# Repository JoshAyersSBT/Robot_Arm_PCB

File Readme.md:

# USB-C PD Powered ESP32 Servo Controller

This document consolidates the **power architecture, wiring, BOM additions, and system diagram** for an ESP32-based robot arm controller using:

* **USB-C Power Delivery (PD)** via **STUSB4500QTR**
* **ESP32** MCU
* **PCA9685** PWM servo controller
* **CH340X** USB-to-UART programmer
* **Cheap / low-load servos** (budget-friendly design)

---

## 1. System Overview

The board negotiates a higher-voltage USB-C PD contract, then generates two isolated rails:

* **SERVO_6V** – high-current rail for servos
* **+3V3** – logic rail for ESP32, PCA9685, and STUSB4500

Key design goal: **prevent ESP32 brownout** caused by servo current spikes.

---

## 2. Power Domains

### Rails

* **VBUS_IN**: USB-C VBUS (5–20V after PD negotiation)
* **VSYS**: Post power-path rail
* **SERVO_6V**: Buck-regulated servo rail
* **+3V3**: Logic rail

### Critical Rules

* ESP32 **must only see 3.3V**
* Servo power **must not be drawn from 3.3V**
* Servo current must not share thin traces or return paths with ESP32 logic ground

---

## 3. Wiring Map (Net-Level)

### USB-C → STUSB4500QTR (PD)

* `USBC_CC1 (A5)  -> STUSB_CC1`
* `USBC_CC2 (B5)  -> STUSB_CC2`
* `USBC_VBUS      -> VBUS_IN`
* `USBC_GND       -> GND`

### USB-C → CH340X (USB2)

* `USBC_D+ (A6/B6 tied) -> CH340_UD+`
* `USBC_D− (A7/B7 tied) -> CH340_UD−`

### CH340X → ESP32 (UART)

* `CH340_TXD -> ESP32_U0RXD (GPIO3)`
* `CH340_RXD -> ESP32_U0TXD (GPIO1)`
* `CH340_DTR/RTS -> ESP32_EN / ESP32_IO0 (auto-program circuit)`

### ESP32 ↔ STUSB4500QTR (I2C + Status)

* `ESP32_GPIO21 (SDA) <-> STUSB_SDA` (pull-up to +3V3)
* `ESP32_GPIO22 (SCL) <-> STUSB_SCL` (pull-up to +3V3)
* `STUSB_ALERT -> ESP32_GPIO (input, optional)`
* `ESP32_GPIO -> STUSB_RESET (optional; otherwise pull-up)`

### ESP32 ↔ PCA9685 (I2C)

* `ESP32_GPIO21 (SDA) <-> PCA_SDA`
* `ESP32_GPIO22 (SCL) <-> PCA_SCL`
* `PCA_VDD -> +3V3`
* `PCA_V+  -> SERVO_6V`
* `PCA_GND -> GND`

### Power Chain

* `VBUS_IN -> Power Path -> VSYS`
* `VSYS -> Buck (6V) -> SERVO_6V`
* `VSYS -> Buck/LDO -> +3V3`

---

## 4. Layout Notes (Brownout Prevention)

* Route **SERVO_6V** with wide copper pours
* Return servo current directly to power entry ground (star-like topology)
* Place **bulk capacitors** close to servo headers
* Isolate logic rail with ferrite bead if needed

---

## 5. BOM Additions (Budget / Low-Load Servo Design)

### 5.1 Servo Rail Buck (VSYS → 6.0V)

**Recommended IC**

* **MP1584EN-LF-Z** – 3A buck regulator (cheap, common)

**Typical Supporting Parts**

* Inductor: 4.7µH, ≥3A shielded
* Input caps: 22–47µF MLCC
* Output caps: 2× 47µF MLCC + bulk electrolytic
* Feedback resistors: set to 6.0V

---

### 5.2 Logic Rail (VSYS → 3.3V)

**Option A (quieter, recommended)**

* Buck to 5V: **MP1584EN**
* LDO to 3.3V: **AP2112K-3.3TRG1** (600mA)

**Option B (fewer parts)**

* Single MP1584EN configured for 3.3V

---

### 5.3 USB Protection

* USB D+/D− ESD: **USBLC6-2SC6**
* CC line ESD (optional): **PESD5V0S1UL** (one per CC)

---

### 5.4 Ferrite Bead (Logic Isolation)

* **BLM21PG600SN1D** (0603)

---

### 5.5 Bulk Capacitors

**Servo Rail**

* 470µF – 2200µF electrolytic or polymer (≥10V)

**Logic Rail**

* 22µF bulk
* 0.1µF decoupling near ESP32 VDD

---

### 5.6 I2C Pull-ups

* SDA: 4.7kΩ to +3V3
* SCL: 4.7kΩ to +3V3

---

### 5.7 Optional Servo Signal Conditioning

* 33–100Ω series resistor on each PCA9685 PWM output

---

## 6. System Wiring Diagram (Mermaid)

```mermaid
flowchart LR
  USBC["USB-C Receptacle P1"]
  PD["STUSB4500QTR U2"]
  PPATH["Power-Path / Protection<br/>(eFuse or Load Switch)"]
  CH340["CH340X U5"]
  ESP["ESP32 U1"]
  PCA["PCA9685 U3"]
  LDO33["3.3V Regulator<br/>(LDO or Buck)"]
  SERVOS["Servo Headers / Servos"]
  ESDUSB["USB ESD<br/>(D+/D−)"]
  ESDCC["CC ESD (opt)"]

  %% ---------------- USB2 PROGRAMMING ----------------
  USBC -->|"A6/B6 D+ → D+ IN"| ESDUSB
  USBC -->|"A7/B7 D− → D− IN"| ESDUSB
  ESDUSB -->|"D+ OUT → UD+"| CH340
  ESDUSB -->|"D− OUT → UD−"| CH340
  CH340 -->|"TXD → ESP GPIO3 U0RXD"| ESP
  CH340 -->|"RXD → ESP GPIO1 U0TXD"| ESP
  CH340 -->|"DTR/RTS → EN/IO0 auto-prog"| ESP

  %% ---------------- USB-C PD NEGOTIATION ----------------
  USBC -->|"A5 CC1 → CC1 IN"| ESDCC
  USBC -->|"B5 CC2 → CC2 IN"| ESDCC
  ESDCC -->|"CC1 OUT → STUSB CC1"| PD
  ESDCC -->|"CC2 OUT → STUSB CC2"| PD

  %% ---------------- POWER PATH (NO BUCK REGULATOR) ----------------
  USBC -->|"VBUS (A4/B4) → VIN"| PPATH
  PD -->|"VBUS_EN_SNK → EN"| PPATH
  PD -->|"DISCH / VBUS_VS_DISCH → Discharge/Sense"| PPATH
  PPATH -->|"VOUT → VSYS (5V rail)"| SERVOS
  PPATH -->|"VOUT → VSYS (5V rail) → PCA V+"| PCA

  %% ---------------- LOGIC POWER ----------------
  PPATH -->|"VSYS (5V) → VIN"| LDO33
  LDO33 -->|"+3V3 → ESP VDD"| ESP
  LDO33 -->|"+3V3 → PCA VDD"| PCA
  LDO33 -->|"+3V3 → STUSB VDD"| PD

  %% ---------------- I2C BUS ----------------
  ESP <-->|"GPIO21 SDA ↔ SDA"| PD
  ESP <-->|"GPIO22 SCL ↔ SCL"| PD
  ESP <-->|"GPIO21 SDA ↔ SDA"| PCA
  ESP <-->|"GPIO22 SCL ↔ SCL"| PCA

  %% ---------------- STATUS / CONTROL ----------------
  PD -->|"ALERT → ESP GPIO (opt)"| ESP
  ESP -->|"GPIO → RESET (opt)"| PD

  %% ---------------- GROUNDS ----------------
  USBC ---|"GND"| PD
  USBC ---|"GND"| PPATH
  USBC ---|"GND"| CH340
  USBC ---|"GND"| ESP
  USBC ---|"GND"| PCA
  USBC ---|"GND"| SERVOS

```

---

## 7. Next Steps

Before PCB layout:

* Confirm **servo count** and **stall current**
* Decide PD voltage request (9V vs 12V)
* Lock in buck inductor + capacitor values per datasheet

Once confirmed, this design is **PCB-ready** for a low-cost, reliable USB-C powered robot arm controller.

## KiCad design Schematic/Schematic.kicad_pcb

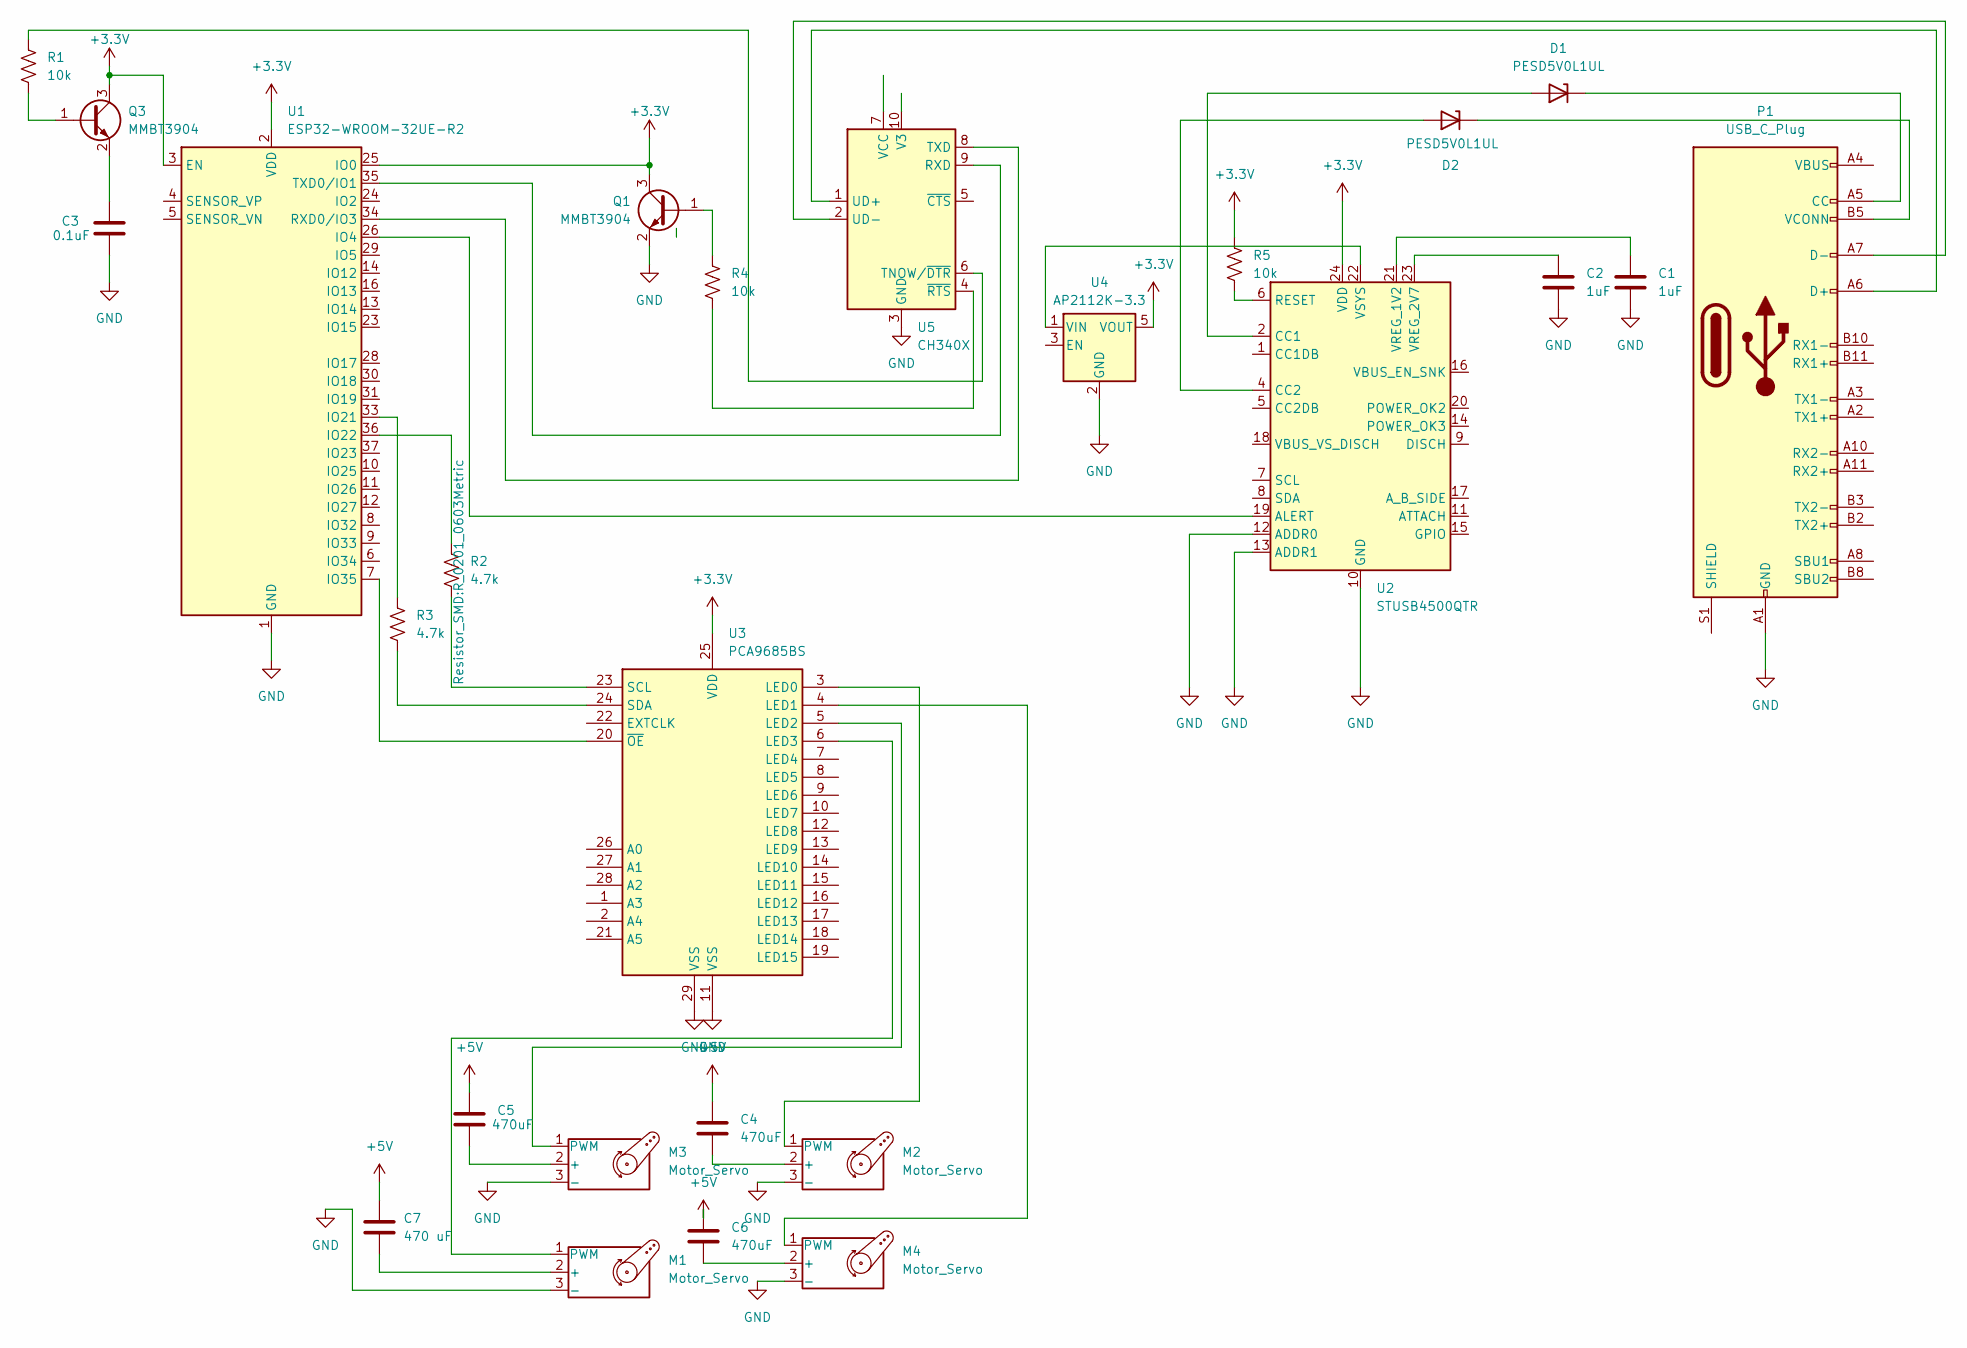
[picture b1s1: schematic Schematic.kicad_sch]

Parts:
C1, C2: 1uF; C_0201_0603Metric
C3: 0.1uF; C_0201_0603Metric
C4, C5, C6: 470uF; C_0201_0603Metric
C7: 470 uF; C_0201_0603Metric
D1, D2: PESD5V0L1UL; D_SOD-882
M1, M2, M3, M4: Motor_Servo; PinHeader_1x03_P2.54mm_Vertical
P1: USB_C_Plug; USB_C_Receptacle_CNCTech_C-ARA1-AK51X
Q1, Q3: MMBT3904; SOT-23
R1, R4, R5: 10k; R_0201_0603Metric
R2, R3: 4.7k; R_0201_0603Metric
U1: ESP32-WROOM-32UE-R2; ESP32-WROOM-32UE
U2: STUSB4500QTR; QFN-24-1EP_4x4mm_P0.5mm_EP2.7x2.7mm
U3: PCA9685BS; QFN-28-1EP_6x6mm_P0.65mm_EP4.25x4.25mm
U4: AP2112K-3.3; SOT-23-5
U5: CH340X; MSOP-10_3x3mm_P0.5mm

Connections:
+3.3V: Q1.3 (C), Q3.3 (C), R5.1, U1.2 (VDD), U1.3 (EN), U1.25 (IO0), U2.24 (VDD), U3.25 (VDD), U4.5 (VOUT)
+5V: C4.1, C5.1, C6.1, C7.1
GND: C1.2, C2.2, C3.2, M1.3 (-), M2.3 (-), M3.3 (-), M4.3 (-), P1.A1 (GND), P1.A12 (GND), P1.B1 (GND), P1.B12 (GND), Q1.2 (E), U1.1 (GND), U1.15 (GND), U1.38 (GND), U1.39 (GND), U2.10 (GND), U2.12 (ADDR0), U2.13 (ADDR1), U2.25 (GND), U3.11 (VSS), U3.29 (VSS), U4.2 (GND), U5.3 (GND)
unnamed: D1.2 (A), U2.2 (CC1)
unnamed: D1.1 (K), P1.A5 (CC)
unnamed: D2.2 (A), U2.4 (CC2)
unnamed: D2.1 (K), P1.B5 (VCONN)
unnamed: C7.2, M1.2 (+)
unnamed: M1.1 (PWM), U3.6 (LED3)
unnamed: C4.2, M2.2 (+)
unnamed: M2.1 (PWM), U3.3 (LED0)
unnamed: C5.2, M3.2 (+)
unnamed: M3.1 (PWM), U3.5 (LED2)
unnamed: C6.2, M4.2 (+)
unnamed: M4.1 (PWM), U3.4 (LED1)
unnamed: P1.A6 (D+), U5.1 (UD+)
unnamed: P1.A7 (D-), U5.2 (UD-)
unnamed: P1.A4 (VBUS), P1.A9 (VBUS), P1.B4 (VBUS), P1.B9 (VBUS)
unnamed: Q1.1 (B), R4.1
unnamed: Q3.1 (B), R1.2
unnamed: C3.1, Q3.2 (E)
unnamed: U1.26 (IO4), U2.19 (ALERT)
unnamed: R3.1, U1.33 (IO21)
unnamed: R2.1, U1.36 (IO22)
unnamed: U1.7 (IO35), U3.20 (~OE)
unnamed: U1.34 (RXD0/IO3), U5.8 (TXD)
unnamed: U1.35 (TXD0/IO1), U5.9 (RXD)
unnamed: R5.2, U2.6 (RESET)
unnamed: C1.1, U2.21 (VREG_1V2)
unnamed: C2.1, U2.23 (VREG_2V7)
unnamed: U2.22 (VSYS), U4.1 (VIN)
unnamed: R2.2, U3.23 (SCL)
unnamed: R3.2, U3.24 (SDA)
unnamed: R1.1, U5.6 (TNOW/~DTR)
unnamed: R4.2, U5.4 (~RTS)

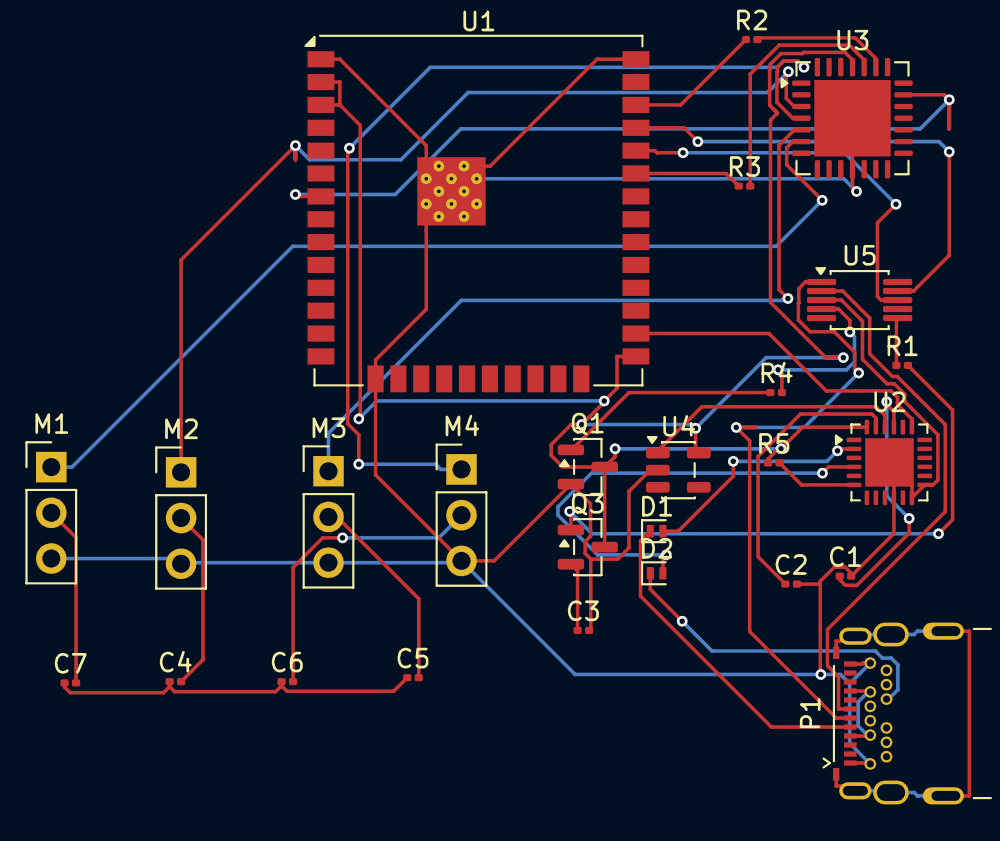
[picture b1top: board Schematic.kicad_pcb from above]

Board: 2 copper layers, 26 parts (0 on the bottom side), 35 nets.

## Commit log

2025-12-29 Added Curcuit board and partial PCB schematic
